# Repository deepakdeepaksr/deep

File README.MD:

morishield is a device for identifying pesticide drift in silk worm farms.for this identification we use a pcb board with sensors and a microcontroller.
a custom pcb, edgehax esp32 s3 (has built-in microSD slot for sensor data logging WHEN NO NETWORK and sync to server later).we use sensors like:
SGP41 — VOC/NOx air-quality (the primary drift signal), SHT45 — temperature/humidity
SPS30 — PM2.5/PM10 particulate, BME688 — gas/VOC
FDC1004 — 4-channel capacitance electrode (deposit on leaf/electrode at 1 m)
soil moisture probe (analog) and FSR (spray impact/weight)
reed switch anemometer for wind speed
GY-521 (MPU-6050) IMU and DS3231 RTC (plug-in modules)
and the carrier adds:
A7672S 4G LTE modem (SIM, J3/J4) + E22-900T22D LoRa (J6) for the uplink
TCA9548A 8-channel I²C multiplexer — each sensor gets its own switched 3.3 V channel (J11/J12/J13/J14/J21 + 2 spare)
TCA9535 16-bit I/O expander, TPS3823-33 watchdog, TPS7A2033 3.3 V LDO
5 V input at J18 with reverse-polarity/over-voltage FET protection, TVS + ESD arrays, PTC and ferrite; PE/earth at J19
user interface: panel LED pair (J24), 5 V buzzer (J25), external button (J23), on-board tactile switch + status LEDs

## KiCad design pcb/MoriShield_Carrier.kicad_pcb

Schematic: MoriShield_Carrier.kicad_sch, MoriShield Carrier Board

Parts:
C1: 10uF/25V; CP_Radial_D5.0mm_P2.50mm
C3, C4, C7, C8, C9, C10, C14, C16, C30, C34, C35, C36, C39, C40, C41, C42, C43, C44, C45, C46, C47, C48, C49, C50, C52, C53, C54, C55, C56, C57, C58, C59, C60, C61, C62, C63, C64, C67: 100nF; C_0805_2012Metric_Pad1.18x1.45mm_HandSolder
C5: 470uF/25V; CP_Radial_D10.0mm_P5.00mm
C13: 10uF/50V_X7R; CP_Radial_D10.0mm_P5.00mm
C26, C27: 1uF/10V; C_0805_2012Metric_Pad1.18x1.45mm_HandSolder
C28, C38: 10uF/10V; C_1206_3216Metric_Pad1.33x1.80mm_HandSolder
C29: 100nF; C_0805_2012Metric_Pad1.18x1.45mm_HandSolder; not fitted
C31: 100uF/16V; CP_Radial_D6.3mm_P2.50mm
C32, C51: 10uF/16V; C_1206_3216Metric_Pad1.33x1.80mm_HandSolder
C33: 100nF/16V; C_0805_2012Metric_Pad1.18x1.45mm_HandSolder
C65: 470uF/16V; CP_Radial_D8.0mm_P3.50mm
C66: 10uF/16V; C_0805_2012Metric_Pad1.18x1.45mm_HandSolder
D2: SMCJ5.0A; D_SMC_Handsoldering
D3: GRN; LED_D3.0mm
D4: YEL; LED_D3.0mm
D6: RED; LED_D3.0mm
D7: SS56; D_SMC_Handsoldering
ESD1, ESD2, ESD7, ESD8, ESD9, ESD10, ESD11, ESD12: SRV05-4; SOT-23-6
ESD3, ESD4, ESD17, ESD18, ESD19, ESD20: PESD5V0S1BA; D_SOD-323
ESD16: SMBJ5.0A; D_SMB_Handsoldering
F1: PTC_4A; Fuseholder_Clip-5x20mm_Littelfuse_111_Inline_P20.00x5.00mm_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; Rating PTC / Slow-Blow >= 40V
FB2: 120R@100MHz 2A; L_0805_2012Metric
H1, H2, H3, H4: M3; MountingHole_3.2mm_M3
J1: Sock_1x22_L; PinSocket_1x22_P2.54mm_Vertical_R180
J2: Sock_1x22_R; PinSocket_1x22_P2.54mm_Vertical_R180
J3: Sock_1x12_L; PinSocket_1x12_P2.54mm_Vertical
J4: Sock_1x12_R; PinSocket_1x12_P2.54mm_Vertical
J5: MX126-5.0-02P; TerminalBlock_MaiXu_MX126-5.0-02P_1x02_P5.00mm_R270
J6: Sock_1x07; PinSocket_1x07_P2.54mm_Vertical_R90
J7: GY-521_MPU6050; PinSocket_1x08_P2.54mm_Vertical
J8: DS3231_RTC; PinSocket_1x06_P2.54mm_Vertical
J11: SGP41; JST_XH_B4B-XH-A_1x04_P2.50mm_Vertical
J12: SHT45; JST_XH_B4B-XH-A_1x04_P2.50mm_Vertical
J13: SPS30_5V; JST_ZH_B5B-ZR_1x05_P1.50mm_Vertical
J14: BME688; JST_XH_B4B-XH-A_1x04_P2.50mm_Vertical
J15: SOIL_ANALOG; JST_XH_B3B-XH-A_1x03_P2.50mm_Vertical
J16: FSR_ANALOG; JST_XH_B2B-XH-A_1x02_P2.50mm_Vertical
J17, J20: JST_XH_4; JST_XH_B4B-XH-A_1x04_P2.50mm_Vertical
J18: ScrewTerm_2; TerminalBlock_MaiXu_MX126-5.0-02P_1x02_P5.00mm_R270
J19: PE/EARTH; TerminalBlock_MaiXu_MX126-5.0-02P_1x02_P5.00mm_R270
J21: FDC1004; JST_XH_B4B-XH-A_1x04_P2.50mm_Vertical
J22: REED_WIND_SPEED; JST_XH_B2B-XH-A_1x02_P2.50mm_Vertical
J23: EXT_BTN; JST_XH_B2B-XH-A_1x02_P2.50mm_Vertical
J24: PANEL_LED_5V; JST_XH_B4B-XH-A_1x04_P2.50mm_Vertical
J25: BUZZER_5V; JST_XH_B2B-XH-A_1x02_P2.50mm_Vertical
J26: AS5600_WIND_DIR; JST_XH_B4B-XH-A_1x04_P2.50mm_Vertical
Q1, Q5, Q6: 2N7000; TO-92_Inline
Q2, Q3, Q7: AO3401A; SOT-23_HS
Q4, Q8: 2N7002; SOT-23_HS
Q9: AO3401A; SOT-23_PMOS_HS
R1, R2: DNP; R_Axial_DIN0207_L6.3mm_D2.5mm_P7.62mm_Horizontal
R5, R10, R13, R14, R49, R51, R52: 10k; R_1206_3216Metric_Pad1.30x1.75mm_HandSolder
R6, R7, R11, R15: 1k; R_1206_3216Metric_Pad1.30x1.75mm_HandSolder
R16, R35, R36, R37, R38, R39, R40, R41, R42, R43, R44, R45, R46, R47, R48: 4.7k; R_1206_3216Metric_Pad1.30x1.75mm_HandSolder
R20, R21, R23, R53, R55: 100k; R_0805_2012Metric_Pad1.20x1.40mm_HandSolder
R22, R24, R54: 10k; R_0805_2012Metric_Pad1.20x1.40mm_HandSolder
R25, R26, R27, R28: 4.7k; R_0805_2012Metric_Pad1.20x1.40mm_HandSolder
R29, R30: 1k; R_0805_2012Metric_Pad1.20x1.40mm_HandSolder
R31, R32, R33, R34: 47R; R_0805_2012Metric_Pad1.20x1.40mm_HandSolder
R50: 100R; R_1206_3216Metric_Pad1.30x1.75mm_HandSolder
R56, R57: 0; R_0603_1608Metric
R58: 100; R_0603_1608Metric
SW1: SW_6x6
TP2, TP3: +5V; TestPoint_Pad_D2.0mm
TP4: 3V3_C; TestPoint_Pad_D2.0mm
TP5: GND; TestPoint_Pad_D2.0mm
TP6: RST_ESP; TestPoint_Pad_D2.0mm
TP7: I2C0_SDA; TestPoint_Pad_D2.0mm
TP8: I2C0_SCL; TestPoint_Pad_D2.0mm
TP9: UART2_MOD_TX; TestPoint_Pad_D2.0mm
TP10: UART2_MOD_RX; TestPoint_Pad_D2.0mm
TP11: I2C0_SDA_CH6; TestPoint_Pad_D2.0mm
TP12: I2C0_SCL_CH6; TestPoint_Pad_D2.0mm
U4: TPS3823-33; SOT-23-5_HS
U6: TPS7A2033; SOT-23-5
U7: TCA9548A; TSSOP-24_4.4x7.8mm_P0.65mm_HS
U8: TCA9535; TSSOP-24_4.4x7.8mm_P0.65mm_HS
U10: eFuse; SOT-23-6

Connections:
+5V_F: F1.2, Q9.2 (S)
+5V_IN: F1.1, J18.1
/3V3_SENS: C27.1, Q2.2 (S), R20.1, U6.5 (OUT)
/3V3_SENS_SW: C43.1, C44.1, C45.1, C47.1, C48.1, C49.1, C50.1, C51.1, C58.1, C59.1, C60.1, C61.1, C62.1, ESD7.4 (IO3), ESD7.5 (VCC), ESD8.4 (IO3), ESD8.5 (VCC), ESD9.4 (IO3), ESD9.5 (VCC), ESD10.4 (IO3), ESD10.5 (VCC), ESD12.4 (IO3), ESD12.5 (VCC), J11.1 (VCC), J12.1 (VCC), J14.1 (VCC), J15.1 (VCC), J16.1, J17.1 (VCC), J20.1 (VCC), J21.1 (VCC), Q2.3 (D), R25.2, R26.2, R27.2, R28.2, R39.2, R40.2, R41.2, R42.2, R43.2, R44.2, R45.2, R46.2, R47.2, R48.2
/+5V_E22: C38.1, C39.1, FB2.2, J6.2 (VCC)
/+5V_E22_IN: FB2.1, Q7.3 (D)
/+5V_ESP: C28.1, C64.1, D7.1 (K), J1.21 (5V)
/+5V_SENS: C31.1, C32.1, C33.1, C46.1, ESD11.4 (IO3), ESD11.5 (VCC), J13.1 (VDD), Q3.3 (D)
/BUZZER_EN: Q1.2 (G), R14.1, U8.18 (P15)
/BZ_NEG: J25.2, Q1.3 (D)
/E22_AUX: J1.9 (IO16), J6.3 (AUX)
/E22_EN: R54.1, U8.6 (P02)
/E22_EN_G: Q8.1 (G), R54.2, R55.1
/E22_GATE: Q7.1 (G), Q8.3 (D), R53.2
/E22_M0_STRAP: J6.7 (M0), R57.1
/E22_M1_STRAP: J6.6 (M1), R56.1
/EVENT_BTN: C16.1, ESD20.1 (K), J1.8 (IO15), J23.1, R10.2, SW1.2 (B)
/FSR_ADC_F: C35.1, J2.4 (IO1), R30.2
/FSR_ADC_RAW: ESD3.1 (K), J16.2, R5.1, R30.1
/I2C0_MUX_SC0: R32.1, U7.5 (SC0)
/I2C0_MUX_SC1: R34.1, U7.7 (SC1)
/I2C0_MUX_SD0: R31.1, U7.4 (SD0)
/I2C0_MUX_SD1: R33.1, U7.6 (SD1)
/I2C0_SCL: ESD1.3 (IO2), J1.15 (IO9), R2.1, R35.1, TP8.1, U7.22 (SCL)
/I2C0_SCL_CH0: ESD7.3 (IO2), J11.3 (SCL), R26.1, R32.2
/I2C0_SCL_CH1: ESD8.3 (IO2), J12.3 (SCL), R28.1, R34.2
/I2C0_SCL_CH2: ESD11.3 (IO2), J13.3 (SCL), R40.1, U7.9 (SC2)
/I2C0_SCL_CH3: ESD10.3 (IO2), J14.3 (SCL), R42.1, U7.11 (SC3)
/I2C0_SCL_CH4: ESD9.3 (IO2), J17.3 (SCL), R44.1, U7.14 (SC4)
/I2C0_SCL_CH5: ESD12.3 (IO2), J21.3 (SCL), R46.1, U7.16 (SC5)
/I2C0_SCL_CH6: ESD19.1 (K), J20.3 (SCL), R48.1, TP12.1, U7.18 (SC6)
/I2C0_SDA: ESD1.1 (IO1), J1.12 (IO8), R1.1, R36.1, TP7.1, U7.23 (SDA)
/I2C0_SDA_CH0: ESD7.1 (IO1), J11.4 (SDA), R25.1, R31.2
/I2C0_SDA_CH1: ESD8.1 (IO1), J12.4 (SDA), R27.1, R33.2
/I2C0_SDA_CH2: ESD11.1 (IO1), J13.2 (SDA), R39.1, U7.8 (SD2)
/I2C0_SDA_CH3: ESD10.1 (IO1), J14.4 (SDA), R41.1, U7.10 (SD3)
/I2C0_SDA_CH4: ESD9.1 (IO1), J17.4 (SDA), R43.1, U7.13 (SD4)
/I2C0_SDA_CH5: ESD12.1 (IO1), J21.4 (SDA), R45.1, U7.15 (SD5)
/I2C0_SDA_CH6: ESD18.1 (K), J20.4 (SDA), R47.1, TP11.1, U7.17 (SD6)
/I2C1_SCL: ESD2.3 (IO2), J1.5 (IO5), J7.6 (SCL), J8.3 (SCL), J26.3 (SCL), R37.1, U8.22 (SCL)
/I2C1_SDA: ESD2.1 (IO1), J1.4 (IO4), J7.5 (SDA), J8.4 (SDA), J26.4 (SDA), R38.1, U8.23 (SDA)
/I2C_SW_RST: C29.1, J1.20 (IO14), R24.2, U7.3 (RESET)
/LED1_K: J24.2 (GND), Q5.3 (D)
/LED2_K: J24.3 (SCL), Q6.3 (D)
/LED_DRV1: Q5.2 (G), R51.1, U8.4 (P00)
/LED_DRV2: Q6.2 (G), R52.1, U8.5 (P01)
/LED_STAT_K: D6.2 (A), R11.2
/MODEM_RST: J1.6 (IO6), R58.1
/MPU_INT: J2.18 (IO21), J7.1 (INT)
/PWR_EN: J1.7 (IO7), J3.1 (PWR_EN), R16.1
/PWR_KEY: J4.1 (PWR_KEY), R15.1
/REED_PULSE: C40.1, ESD17.1 (K), J22.1, R49.1, R50.1
/REED_PULSE_F: J2.9 (IO39), R50.2
/RST_ESP: J1.3 (RST), TP6.1, U4.1 (RESET)
/SENS_EN: R22.1, U8.19 (P16)
/SENS_EN_G: Q4.1 (G), R22.2, R23.1
/SENS_GATE: Q2.1 (G), Q3.1 (G), Q4.3 (D), R20.2, R21.2
/SOIL_ADC_F: C34.1, J2.5 (IO2), R29.2
/SOIL_ADC_RAW: ESD4.1 (K), J15.3 (OUT), R29.1
/STATUS_LED: J2.6 (IO42), R11.1
/UART1_LORA_RX: J1.11 (IO18), J6.4 (TXD)
/UART1_LORA_TX: J1.10 (IO17), J6.5 (RXD)
/UART2_MOD_RX: J2.16 (IO48), J4.4 (TXD), TP10.1
/UART2_MOD_TX: J2.17 (IO47), J4.5 (RXD), TP9.1
/WDT_MR: R13.2, U4.3 (MR)
/WDT_WDI: U4.4 (WDI), U8.11 (P07)
GND: C1.2, C3.2, C4.2, C5.2, C7.2, C8.2, C9.2, C10.2, C13.2, C14.2, C16.2, C26.2, C27.2, C28.2, C29.2, C30.2, C31.2, C32.2, C33.2, C34.2, C35.2, C36.2, C38.2, C39.2, C40.2, C41.2, C42.2, C43.2, C44.2, C45.2, C46.2, C47.2, C48.2, C49.2, C50.2, C51.2, C52.2, C53.2, C54.2, C55.2, C56.2, C57.2, C58.2, C59.2, C60.2, C61.2, C62.2, C63.2, C64.2, C65.2, C66.2, C67.2, D2.2 (A2), D3.1 (K), D4.1 (K), D6.1 (K), ESD1.2 (GND), ESD2.2 (GND), ESD16.2 (A), J1.22 (GND), J2.1 (GND), J2.21 (GND), J2.22 (GND), J3.6 (GND), J3.9 (GND), J3.12 (GND), J4.2 (GND), J4.6 (GND), J4.12 (GND), J5.2, J6.1 (GND), J7.7 (GND), J8.6 (GND), J11.2 (GND), J12.2 (GND), J13.4 (SEL), J13.5 (GND), J14.2 (GND), J15.2 (GND), J17.2 (GND), J18.2, J19.2, J20.2 (GND), J21.2 (GND), J22.2, J23.2, J24.4 (SDA), J26.2 (GND), Q1.1 (S), Q4.2 (S), Q5.1 (S), Q6.1 (S), Q8.2 (S), Q9.1 (G), R5.2, R14.2, R15.2, R16.2, R23.2, R51.2, R52.2, R55.2, R56.2, R57.2, SW1.1 (A), TP5.1, U4.2 (GND), U6.2 (GND), U7.1 (A0), U7.2 (A1), U7.12 (GND), U7.21 (A2), U8.2 (A1), U8.3 (A2), U8.12 (GND), U8.21 (A0)
LED5V_A: D3.2 (A), R6.1
LED33_A: D4.2 (A), R7.1
unnamed: J4.8 (RESET), R58.2

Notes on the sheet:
!padne CURRENT i=0.15A f=J6.2 t=J6.1
I2C BUSES, 8-CH MUX and IO EXPANDER
!padne REGULATOR p=U1.2 n=U1.1 f=U1.1 t=U1.3 v=3.3 gain=1
!padne CURRENT i=0.012A f=R7.2 t=D4.1
!padne CURRENT i=0.003A f=J8.5 t=J8.6
!padne CURRENT i=2.0A f=J5.1 t=J5.2
ESP32 HOST CARRIER
!padne CURRENT i=0.05A f=J11.1,J12.1,J14.1,J17.1,J15.1,J16.1 t=J11.2,J12.2,J14.2,J17.2,J15.2,J16.2 coupling=1
I2C SENSOR CHANNELS CH0 - CH6
!padne CURRENT i=0.004A f=J7.8 t=J7.7
POWER INPUT and REVERSE-POLARITY PROTECTION
!padne CURRENT i=0.5A f=J1.21 t=J1.22,J2.1,J2.21,J2.22 coupling=0.05
TEST POINTS
ANALOG FRONT-END (FSR / SOIL MOISTURE)
!padne VOLTAGE v=12V p=J18.1 n=J18.2
!padne RESISTANCE r=0.3 a=D1.2 b=D1.1
WIND SENSOR (REED)
SENSOR RAIL REGULATION and POWER SWITCHING
!padne REGULATOR p=J9.1 n=J9.2 f=J9.2 t=J9.3 v=5 gain=0.46
!padne RESISTANCE r=0.05 a=F1.1 b=F1.2
E22 LORA POWER RAIL
!padne CURRENT i=0.012A f=R6.2 t=D3.1
MODULE SOCKETS (LORA / IMU / I2C1)
USER INTERFACE (BUTTON / STATUS LED / ADDRESSABLE LEDS / BUZZER)
POWER BUDGET DIRECTIVES (!padne) - some cite refs removed in Rev 0.2
!padne CURRENT i=0.08A f=J13.1 t=J13.5
WATCHDOG and RESET

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
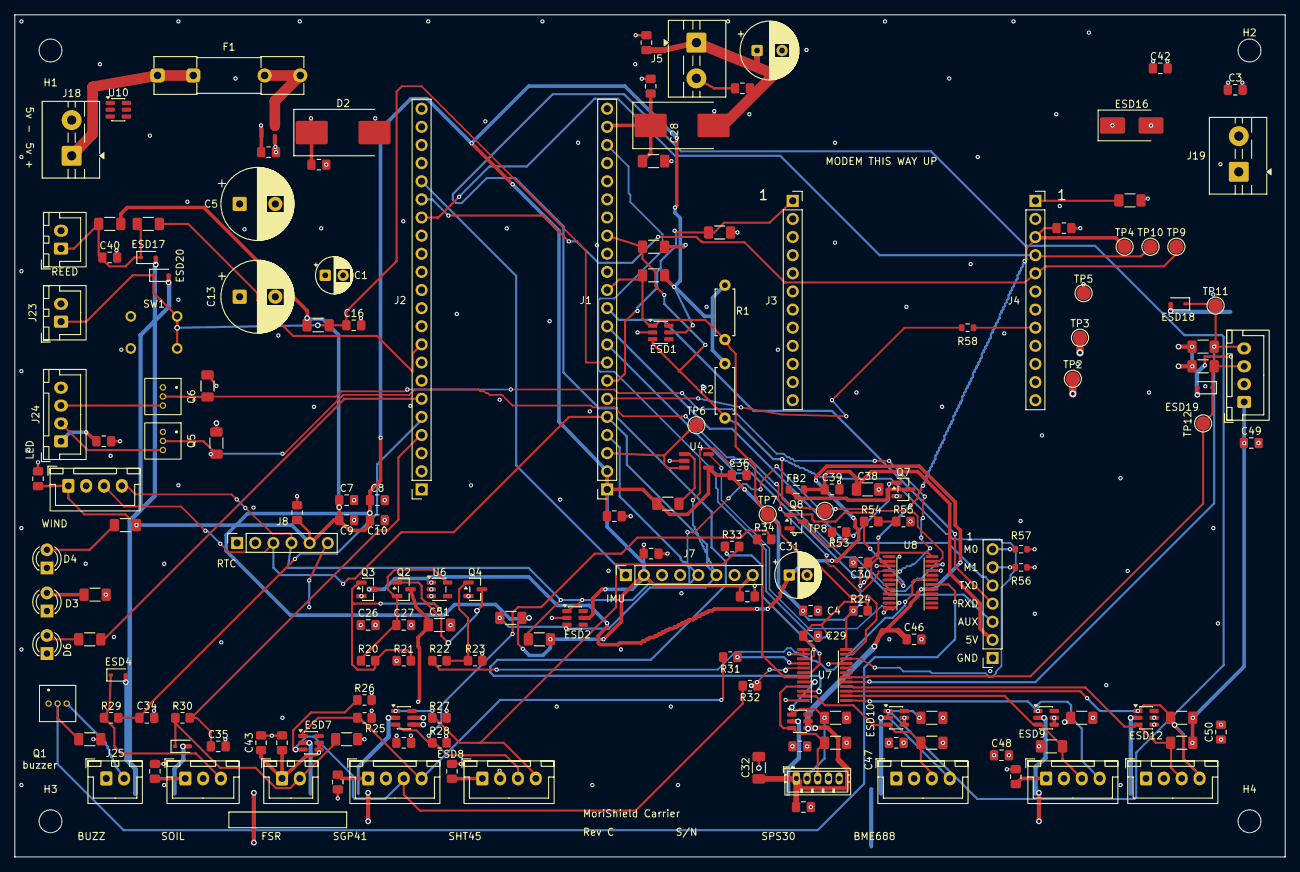
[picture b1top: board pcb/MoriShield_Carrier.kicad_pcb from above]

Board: 4 copper layers, 178.0 x 118.0 mm, 178 parts (0 on the bottom side), 73 nets.

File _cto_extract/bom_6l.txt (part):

C1     | MoriShield_Carrier:CP_Radial_D5.0mm_P2.50mm                            | 10uF/25V
C3     | C_0805_2012Metric_Pad1.18x1.45mm_HandSolder                            | 100nF
C4     | C_0805_2012Metric_Pad1.18x1.45mm_HandSolder                            | 100nF
C5     | MoriShield_Carrier:CP_Radial_D10.0mm_P5.00mm                           | 470uF/25V
C7     | C_0805_2012Metric_Pad1.18x1.45mm_HandSolder                            | 100nF
C8     | C_0805_2012Metric_Pad1.18x1.45mm_HandSolder                            | 100nF
C9     | C_0805_2012Metric_Pad1.18x1.45mm_HandSolder                            | 100nF
C10    | C_0805_2012Metric_Pad1.18x1.45mm_HandSolder                            | 100nF
C13    | CP_Radial_D10.0mm_P5.00mm                                              | 10uF/50V_X7R
C14    | C_0805_2012Metric_Pad1.18x1.45mm_HandSolder                            | 100nF
C16    | C_0805_2012Metric_Pad1.18x1.45mm_HandSolder                            | 100nF
C26    | C_0805_2012Metric_Pad1.18x1.45mm_HandSolder                            | 1uF/10V
C27    | C_0805_2012Metric_Pad1.18x1.45mm_HandSolder                            | 1uF/10V
C28    | C_1206_3216Metric_Pad1.33x1.80mm_HandSolder                            | 10uF/10V
C29    | C_0805_2012Metric_Pad1.18x1.45mm_HandSolder                            | 100nF
C30    | C_0805_2012Metric_Pad1.18x1.45mm_HandSolder                            | 100nF
C31    | CP_Radial_D6.3mm_P2.50mm                                               | 100uF/16V
C32    | C_1206_3216Metric_Pad1.33x1.80mm_HandSolder                            | 10uF/16V
C33    | C_0805_2012Metric_Pad1.18x1.45mm_HandSolder                            | 100nF/16V
C34    | C_0805_2012Metric_Pad1.18x1.45mm_HandSolder                            | 100nF
C35    | C_0805_2012Metric_Pad1.18x1.45mm_HandSolder                            | 100nF
C36    | C_0805_2012Metric_Pad1.18x1.45mm_HandSolder                            | 100nF
C38    | C_1206_3216Metric_Pad1.33x1.80mm_HandSolder                            | 10uF/10V
C39    | C_0805_2012Metric_Pad1.18x1.45mm_HandSolder                            | 100nF
C40    | C_0805_2012Metric_Pad1.18x1.45mm_HandSolder                            | 100nF
C41    | C_0805_2012Metric_Pad1.18x1.45mm_HandSolder                            | 100nF
C42    | C_0805_2012Metric_Pad1.18x1.45mm_HandSolder                            | 100nF
C43    | C_0805_2012Metric_Pad1.18x1.45mm_HandSolder                            | 100nF
C44    | C_0805_2012Metric_Pad1.18x1.45mm_HandSolder                            | 100nF
C45    | C_0805_2012Metric_Pad1.18x1.45mm_HandSolder                            | 100nF
C46    | C_0805_2012Metric_Pad1.18x1.45mm_HandSolder                            | 100nF
C47    | C_0805_2012Metric_Pad1.18x1.45mm_HandSolder                            | 100nF
C48    | C_0805_2012Metric_Pad1.18x1.45mm_HandSolder                            | 100nF
C49    | C_0805_2012Metric_Pad1.18x1.45mm_HandSolder                            | 100nF
C50    | C_0805_2012Metric_Pad1.18x1.45mm_HandSolder                            | 100nF
C51    | C_1206_3216Metric_Pad1.33x1.80mm_HandSolder                            | 10uF/16V
D2     | D_SMC_Handsoldering                                                    | SMCJ5.0A
D3     | MoriShield_Carrier:LED_D3.0mm                                          | GRN
D4     | MoriShield_Carrier:LED_D3.0mm                                          | YEL
D6     | MoriShield_Carrier:LED_D3.0mm                                          | RED
D7     | D_SMC_Handsoldering                                                    | SS56
ESD1   | SOT-23-6                                                               | SRV05-4
ESD2   | SOT-23-6                                                               | SRV05-4
ESD3   | D_SOD-323                                                              | PESD5V0S1BA
ESD4   | D_SOD-323                                                              | PESD5V0S1BA
ESD7   | SOT-23-6                                                               | SRV05-4
ESD8   | SOT-23-6                                                               | SRV05-4
ESD9   | SOT-23-6                                                               | SRV05-4
ESD10  | SOT-23-6                                                               | SRV05-4
ESD11  | SOT-23-6                                                               | SRV05-4
ESD12  | SOT-23-6                                                               | SRV05-4
ESD16  | D_SMB_Handsoldering                                                    | SMBJ5.0A
ESD17  | D_SOD-323                                                              | PESD5V0S1BA
ESD18  | D_SOD-323                                                              | PESD5V0S1BA
ESD19  | D_SOD-323                                                              | PESD5V0S1BA
ESD20  | D_SOD-323                                                              | PESD5V0S1BA
F1     | MoriShield_Carrier:Fuseholder_Clip-5x20mm_Littelfuse_111_Inline_P20.00x5.00mm_D1.05mm_Horizontal | PTC_4A
FB2    | L_0805_2012Metric                                                      | 120R@100MHz 2A
H1     | MountingHole_3.2mm_M3                                                  | M3
H2     | MountingHole_3.2mm_M3                                                  | M3
H3     | MountingHole_3.2mm_M3                                                  | M3
H4     | MountingHole_3.2mm_M3                                                  | M3
J1     | MoriShield_Carrier:PinSocket_1x22_P2.54mm_Vertical_R180                | Sock_1x22_L
J2     | MoriShield_Carrier:PinSocket_1x22_P2.54mm_Vertical_R180                | Sock_1x22_R
J3     | MoriShield_Carrier:PinSocket_1x12_P2.54mm_Vertical                     | Sock_1x12_L
J4     | MoriShield_Carrier:PinSocket_1x12_P2.54mm_Vertical                     | Sock_1x12_R
J5     | MoriShield_Carrier:TerminalBlock_MaiXu_MX126-5.0-02P_1x02_P5.00mm_R270 | MX126-5.0-02P
J6     | MoriShield_Carrier:PinSocket_1x07_P2.54mm_Vertical_R90                 | Sock_1x07
J7     | MoriShield_Carrier:PinSocket_1x08_P2.54mm_Vertical                     | Sock_1x08
J8     | MoriShield_Carrier:PinSocket_1x06_P2.54mm_Vertical                     | Sock_1x06
J11    | MoriShield_Carrier:JST_XH_B4B-XH-A_1x04_P2.50mm_Vertical               | JST_XH_4
J12    | MoriShield_Carrier:JST_XH_B4B-XH-A_1x04_P2.50mm_Vertical               | JST_XH_4
J13    | MoriShield_Carrier:JST_ZH_B5B-ZR_1x05_P1.50mm_Vertical                 | JST_ZH_5
J14    | MoriShield_Carrier:JST_XH_B4B-XH-A_1x04_P2.50mm_Vertical               | JST_XH_4
J15    | MoriShield_Carrier:JST_XH_B3B-XH-A_1x03_P2.50mm_Vertical               | JST_XH_3
J16    | MoriShield_Carrier:JST_XH_B2B-XH-A_1x02_P2.50mm_Vertical               | JST_XH_2
J17    | MoriShield_Carrier:JST_XH_B4B-XH-A_1x04_P2.50mm_Vertical               | JST_XH_4
J18    | MoriShield_Carrier:TerminalBlock_MaiXu_MX126-5.0-02P_1x02_P5.00mm_R270 | ScrewTerm_2
J19    | MoriShield_Carrier:TerminalBlock_MaiXu_MX126-5.0-02P_1x02_P5.00mm_R270 | PE/EARTH
J20    | MoriShield_Carrier:JST_XH_B4B-XH-A_1x04_P2.50mm_Vertical               | JST_XH_4
J21    | JST_XH_B4B-XH-A_1x04_P2.50mm_Vertical                                  | FDC1004
J22    | MoriShield_Carrier:JST_XH_B2B-XH-A_1x02_P2.50mm_Vertical               | JST_XH_2
J23    | MoriShield_Carrier:JST_XH_B2B-XH-A_1x02_P2.50mm_Vertical               | EXT_BTN
J24    | MoriShield_Carrier:JST_XH_B4B-XH-A_1x04_P2.50mm_Vertical               | PANEL_LED_5V
J25    | MoriShield_Carrier:JST_XH_B2B-XH-A_1x02_P2.50mm_Vertical               | BUZZER_5V
Q1     | TO-92_Inline                                                           | 2N7000
Q2     | SOT-23                                                                 | AO3401A
Q3     | SOT-23                                                                 | AO3401A
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
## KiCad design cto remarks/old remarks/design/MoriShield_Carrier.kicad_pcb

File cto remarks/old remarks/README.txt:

================================================================
MoriShield Carrier PCB — Review & Fabrication Package
Board: MoriShield_Carrier | KiCad 10.0.x | 2026-10-12
================================================================

This package contains everything needed to review and fabricate
the MoriShield carrier PCB.

CONTENTS
--------
design/
    MoriShield_Carrier.kicad_pro        KiCad project
    MoriShield_Carrier.kicad_sch        Schematic (ERC-clean)
    MoriShield_Carrier.kicad_pcb        Routed PCB (DRC-clean)
    MoriShield_Carrier.kicad_sym        Project symbol library
    MoriShield_Carrier.pretty/          Project footprint library
    fp-lib-table, sym-lib-table         Library tables (self-contained
                                        project — no external libs needed)

fabrication/
    Gerber set (RS-274X) + Excellon drill file — the exact files
    to send to the fab.

reports/
    MoriShield_Carrier-drc.rpt          0 violations / 0 unconnected
    MoriShield_Carrier-erc.rpt          0 errors / 7 intentional
                                        warnings (unconnected spare
                                        socket pins + PWR_FLAG notes)

MoriShield_Carrier_BOM.csv                Bill of materials
MoriShield_Carrier_positions.csv          Component placement
MoriShield_Carrier_schematic.pdf          Schematic print
renders/top.png, bottom.png               3D renders of routed board

FAB SPECIFICATION
-----------------
    Layers          2 (F.Cu + B.Cu)
    Board size      168 x 118 mm
    Thickness       1.6 mm
    Copper          1 oz (35 um) outer
    Min track       0.30 mm signal / up to 2.2 mm power
    Min clearance   0.18 mm (JLCPCB-compatible; DRC-verified)
    Min drill       0.45 mm via / 0.73 mm JST ZH / 0.95 mm sockets
                    / 3.2 mm mounting
    Surface finish  HASL lead-free (or ENIG — no BGA/fine-pitch)
    Solder mask     green (any)
    Silkscreen      white (top + bottom)
    Stencil         not required — hand-solder assembly
                    (0402/1206/SOT-89 footprints are handsolder-grade)

ASSEMBLY NOTES
--------------
- THT assembly except: C3/C4/C7-C10 (0402), R5/R6/R7 (1206),
  D2 (SMB), ESD1-4 (DFN1006-2), U1 (SOT-89) — all handsolder pads.
- Module sockets (J1-J9) take standard 2.54 mm female headers;
  plug-in modules: EdgeHax S3-PRO, Parry A7672S modem, buck
  converter, MPU6050, RTC, E22 LoRa.
- External sensors via JST (XH 2.5 mm / ZH 1.5 mm) at J11-J18.
- 5x20 mm fuse clip at F1 (5 A glass fuse).
- 4x M3 mounting holes (3.2 mm).

VALIDATION SUMMARY (all passed on this exact board)
---------------------------------------------------
    KiCad DRC          0 violations, 0 unconnected (severity-all,
                       zones refilled)
    KiCad ERC          0 errors, 7 intentional warnings
    Custom audit       33/33 checks (pad parity vs netlist,
                       connectivity union-find, geometry, stackup,
                       RF antenna keepout, per-net widths)
    Fab DFM presets    clean on JLCPCB standard+advanced,
                       PCBWay, OSH Park
    HQ DFM (offline)   0 errors (9 informational hole records)
    Power integrity    FEM DC solve (KiPIDA + padne):
                       +5 V at modem J5 = 4.85 V @ 2 A GSM burst,
                       +12 V chain drop <0.5 V, 3V3_C = 3.293 V,
                       GND bounce ~2 mV

POWER ARCHITECTURE
------------------
    12 V in (J18 screw term) -> F1 5 A -> D1 SB560 (rev-polarity)
    -> buck module (J9 socket) -> +5 V rail -> AMS1117 (U1)
    -> 3V3_C rail for sensor loads.
    GSM modem (J5) is on +5 V with 470 uF bulk at C5.
    12 V TVS SMBJ12CA (D2) on input.

ITEMS TO CONFIRM BEFORE MASS ORDER (physical, not software-checkable)
-------------------------------------------------------------------
1. Buck module pin order — board expects VO+/GND/IN+ single row + EN.
2. Parry A7672S modem footprint — 9-pin + 2-pin rows; board row
   gap is 33.56 mm (J3-J4). Verify against physical module.
3. EdgeHax S3-PRO pin map — GPIO21/22 = I2C-0, 47/48 = I2C-1, 18 = EN;
   board row gap is 26.0 mm (J1-J2). Verify against physical module.
4. GY-521 MPU6050 and E22 module pin orders/orientation.
5. Plug-in modules' own I2C pull-ups (they parallel with R1/R2 1k8,
   R3/R4 4k7 — check total sink current stays <3 mA/line).
6. Enclosure fit: 168 x 118 mm board + standoff clearance.

KNOWN/ACCEPTED LIMITATIONS
--------------------------
- +5 V at J5 ~4.85 V under sustained 2 A burst — within module
  tolerance; keep J5 cable short or add local bulk cap if margin
  is a concern.
- AMS1117 ~90 C at sustained 600 mA (fine for WiFi duty cycles).
- Schematic text lines beginning with "!padne" are power-solver
  annotations (source/load/regulator intent) — harmless, can be
  deleted if they clutter the review.

================================================================

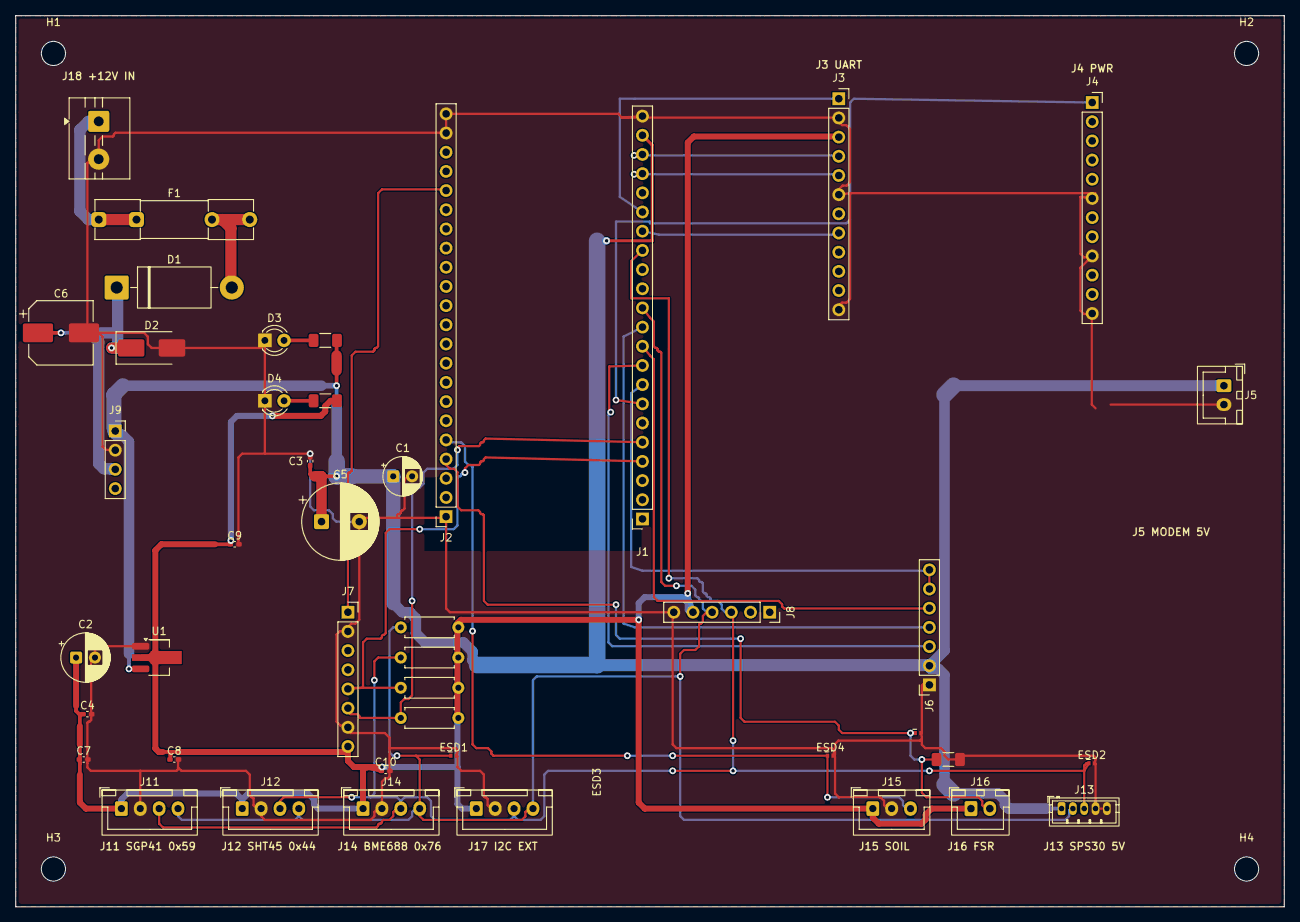
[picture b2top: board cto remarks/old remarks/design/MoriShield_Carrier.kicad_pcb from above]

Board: 2 copper layers, 168.0 x 118.0 mm, 48 parts (0 on the bottom side), 24 nets.

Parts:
C1: 10uF/25V; CP_Radial_D5.0mm_P2.50mm
C2: 22uF/10V; CP_Radial_D6.3mm_P2.50mm
C3: 100nF; C_0402_1005Metric_Pad0.74x0.62mm_HandSolder_R90
C4, C7, C8, C9, C10: 100nF; C_0402_1005Metric_Pad0.74x0.62mm_HandSolder
C5: 470uF/10V; CP_Radial_D10.0mm_P5.00mm
C6: VEJ 100uF/25V; CP_Elec_8x6.5
D1: SB560; D_DO-201AD_P15.24mm_Horizontal
D2: SMBJ12CA; D_SMB_Handsoldering
D3: GRN; LED_D3.0mm
D4: YEL; LED_D3.0mm
ESD1, ESD2, ESD3, ESD4: ESD5V0-DNP; DFN1006-2
F1: 5A; Fuseholder_Clip-5x20mm_Littelfuse_111_Inline_P20.00x5.00mm_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
H1, H2, H3, H4: M3; MountingHole_3.2mm_M3
J1, J2: PinSocket_1x22_P2.54mm_Vertical_R180
J3, J4: PinSocket_1x12_P2.54mm_Vertical
J5: JST_XH_B2B-XH-A_1x02_P2.50mm_Vertical_R270
J6: PinSocket_1x07_P2.54mm_Vertical_R90
J7: PinSocket_1x08_P2.54mm_Vertical
J8: PinSocket_1x06_P2.54mm_Vertical
J9: PinSocket_1x04_P2.54mm_Vertical
J11, J12, J14, J17: JST_XH_B4B-XH-A_1x04_P2.50mm_Vertical
J13: JST_ZH_B5B-ZR_1x05_P1.50mm_Vertical
J15: JST_XH_B3B-XH-A_1x03_P2.50mm_Vertical
J16: JST_XH_B2B-XH-A_1x02_P2.50mm_Vertical
J18: TerminalBlock_MaiXu_MX126-5.0-02P_1x02_P5.00mm_R2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; TerminalBlock_MaiXu_MX126-5.0-02P_1x02_P5.00mm_R270
R1, R2: 1k8; R_Axial_DIN0207_L6.3mm_D2.5mm_P7.62mm_Horizontal
R3, R4: 4k7; R_Axial_DIN0207_L6.3mm_D2.5mm_P7.62mm_Horizontal
R5: 10k; R_1206_3216Metric_Pad1.30x1.75mm_HandSolder
R6, R7: 1k; R_1206_3216Metric_Pad1.30x1.75mm_HandSolder
U1: AMS1117-3.3; SOT-89-3_Handsoldering

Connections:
3V3_C: C2.1, C4.1, C7.1, C8.1, C9.1, C10.1, J3.3, J7.8, J8.5, J11.1, J12.1, J14.1, J15.1, J16.1, J17.1, R1.2, R2.2, R3.2, R4.2, R7.2, U1.2
+5V: C1.1, C3.1, C5.1, J1.21, J5.1, J6.2, J9.1, J13.1, R6.2, U1.3
+12V: C6.1, D1.1, D2.1, J9.3
+12V_F: D1.2, F1.2
+12V_IN: F1.1, J18.1
E22_AUX: J1.9, J6.3
E22_M0M1: J1.8, J6.6, J6.7
FSR_ADC: ESD3.1, J2.4, J16.2, R5.1
GND: C1.2, C2.2, C3.2, C4.2, C5.2, C6.2, C7.2, C8.2, C9.2, C10.2, D2.2, D3.1, D4.1, ESD1.2, ESD2.2, ESD3.2, ESD4.2, J1.22, J2.1, J2.21, J2.22, J3.2, J3.6, J3.12, J4.6, J4.9, J4.12, J5.2, J6.1, J7.2, J7.7, J8.6, J9.2, J11.2, J12.2, J13.4, J13.5, J14.2, J15.2, J17.2, J18.2, R5.2, U1.1
LED5V_A: D3.2, R6.1
LED33_A: D4.2, R7.1
MODEM_RESET: J1.16, J3.8
MPU_INT: J2.18, J7.1
PWRKEY: J1.17, J3.1
PWR_EN: J1.7, J4.1
RX1_LORA: J1.11, J6.4
RX2_MODEM: J1.20, J3.4
SCL0: ESD2.1, J1.15, J8.3, J11.3, J12.3, J13.3, J14.3, J17.3, R2.1
SCL1: J1.5, J7.6, R4.1
SDA0: ESD1.1, J1.12, J8.4, J11.4, J12.4, J13.2, J14.4, J17.4, R1.1
SDA1: J1.4, J7.5, R3.1
SOIL_ADC: ESD4.1, J2.5, J15.3
TX1_LORA: J1.10, J6.5
TX2_MODEM: J1.19, J3.5

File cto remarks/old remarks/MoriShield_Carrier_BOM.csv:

"Refs","Value","Footprint","Qty","DNP"
"C1","10uF/25V","MoriShield_Carrier:CP_Radial_D5.0mm_P2.50mm","1",""
"C2","22uF/10V","MoriShield_Carrier:CP_Radial_D6.3mm_P2.50mm","1",""
"C3","100nF","MoriShield_Carrier:C_0402_1005Metric_Pad0.74x0.62mm_HandSolder_R90","1",""
"C4","100nF","MoriShield_Carrier:C_0402_1005Metric_Pad0.74x0.62mm_HandSolder","1",""
"C5","470uF/10V","MoriShield_Carrier:CP_Radial_D10.0mm_P5.00mm","1",""
"C6","VEJ 100uF/25V","MoriShield_Carrier:CP_Elec_8x6.5","1",""
"C7","100nF","MoriShield_Carrier:C_0402_1005Metric_Pad0.74x0.62mm_HandSolder","1",""
"C8","100nF","MoriShield_Carrier:C_0402_1005Metric_Pad0.74x0.62mm_HandSolder","1",""
"C9","100nF","MoriShield_Carrier:C_0402_1005Metric_Pad0.74x0.62mm_HandSolder","1",""
"C10","100nF","MoriShield_Carrier:C_0402_1005Metric_Pad0.74x0.62mm_HandSolder","1",""
"D1","SB560","MoriShield_Carrier:D_DO-201AD_P15.24mm_Horizontal","1",""
"D2","SMBJ12CA","MoriShield_Carrier:D_SMB_Handsoldering","1",""
"D3","GRN","MoriShield_Carrier:LED_D3.0mm","1",""
"D4","YEL","MoriShield_Carrier:LED_D3.0mm","1",""
"ESD1","D","MoriShield_Carrier:DFN1006-2","1",""
"ESD2","D","MoriShield_Carrier:DFN1006-2","1",""
"ESD3","D","MoriShield_Carrier:DFN1006-2","1",""
"ESD4","D","MoriShield_Carrier:DFN1006-2","1",""
"F1","5A","MoriShield_Carrier:Fuseholder_Clip-5x20mm_Littelfuse_111_Inline_P20.00x5.00mm_D1.05mm_Horizontal","1",""
"J1","Sock_1x22_L","MoriShield_Carrier:PinSocket_1x22_P2.54mm_Vertical_R180","1",""
"J2","Sock_1x22_R","MoriShield_Carrier:PinSocket_1x22_P2.54mm_Vertical_R180","1",""
"J3","Sock_1x12_L","MoriShield_Carrier:PinSocket_1x12_P2.54mm_Vertical","1",""
"J4","Sock_1x12_R","MoriShield_Carrier:PinSocket_1x12_P2.54mm_Vertical","1",""
"J5","JST_XH_2","MoriShield_Carrier:JST_XH_B2B-XH-A_1x02_P2.50mm_Vertical_R270","1",""
"J6","Sock_1x07","MoriShield_Carrier:PinSocket_1x07_P2.54mm_Vertical_R90","1",""
"J7","Sock_1x08","MoriShield_Carrier:PinSocket_1x08_P2.54mm_Vertical","1",""
"J8","Sock_1x06","MoriShield_Carrier:PinSocket_1x06_P2.54mm_Vertical","1",""
"J9","Sock_1x04","MoriShield_Carrier:PinSocket_1x04_P2.54mm_Vertical","1",""
"J11","JST_XH_4","MoriShield_Carrier:JST_XH_B4B-XH-A_1x04_P2.50mm_Vertical","1",""
"J12","JST_XH_4","MoriShield_Carrier:JST_XH_B4B-XH-A_1x04_P2.50mm_Vertical","1",""
"J13","JST_ZH_5","MoriShield_Carrier:JST_ZH_B5B-ZR_1x05_P1.50mm_Vertical","1",""
"J14","JST_XH_4","MoriShield_Carrier:JST_XH_B4B-XH-A_1x04_P2.50mm_Vertical","1",""
"J15","JST_XH_3","MoriShield_Carrier:JST_XH_B3B-XH-A_1x03_P2.50mm_Vertical","1",""
"J16","JST_XH_2","MoriShield_Carrier:JST_XH_B2B-XH-A_1x02_P2.50mm_Vertical","1",""
"J17","JST_XH_4","MoriShield_Carrier:JST_XH_B4B-XH-A_1x04_P2.50mm_Vertical","1",""
"J18","ScrewTerm_2","MoriShield_Carrier:TerminalBlock_MaiXu_MX126-5.0-02P_1x02_P5.00mm_R270","1",""
"R1","1k8","MoriShield_Carrier:R_Axial_DIN0207_L6.3mm_D2.5mm_P7.62mm_Horizontal","1",""
"R2","1k8","MoriShield_Carrier:R_Axial_DIN0207_L6.3mm_D2.5mm_P7.62mm_Horizontal","1",""
"R3","4k7","MoriShield_Carrier:R_Axial_DIN0207_L6.3mm_D2.5mm_P7.62mm_Horizontal","1",""
"R4","4k7","MoriShield_Carrier:R_Axial_DIN0207_L6.3mm_D2.5mm_P7.62mm_Horizontal","1",""
"R5","10k","MoriShield_Carrier:R_1206_3216Metric_Pad1.30x1.75mm_HandSolder","1",""
"R6","1k","MoriShield_Carrier:R_1206_3216Metric_Pad1.30x1.75mm_HandSolder","1",""
"R7","1k","MoriShield_Carrier:R_1206_3216Metric_Pad1.30x1.75mm_HandSolder","1",""
"U1","AMS1117-3.3","MoriShield_Carrier:SOT-89-3_Handsoldering","1",""

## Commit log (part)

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2026-04-20 Updated index.html
